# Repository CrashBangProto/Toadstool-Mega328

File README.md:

#Toadstool-Mega328

**Toadstool Development Board - ATmega328P**

The Toadstool family is made up of breadboard-friendly prototyping boards that house a microcontroller, and modules called *Caps* that connect using a standard header.  The prototyping board is analagous to an Arduino/Launchpad and the Cap analagous to a shield/boosterpack.

This repository contains the schematics for the **Toadstool-Mega328** prototyping board, a breadboard-friendly PCB that houses the ATmega328P microcontroller (or other Atmel pin-compatible variants such as the ATmega8/48/88/168/328).

The boards were layed out using [KiCad](http://www.kicad-pcb.org) - KiCad is open source and awesome.

There are a number of other CrashBangProto respositories containing the schematics for other Toadstool boards and Caps, as well as sample code to get you up and running.

Visit the [Toadstool Webpages](http://www.crash-bang.com/projects/toadstool/) for more information on the project.

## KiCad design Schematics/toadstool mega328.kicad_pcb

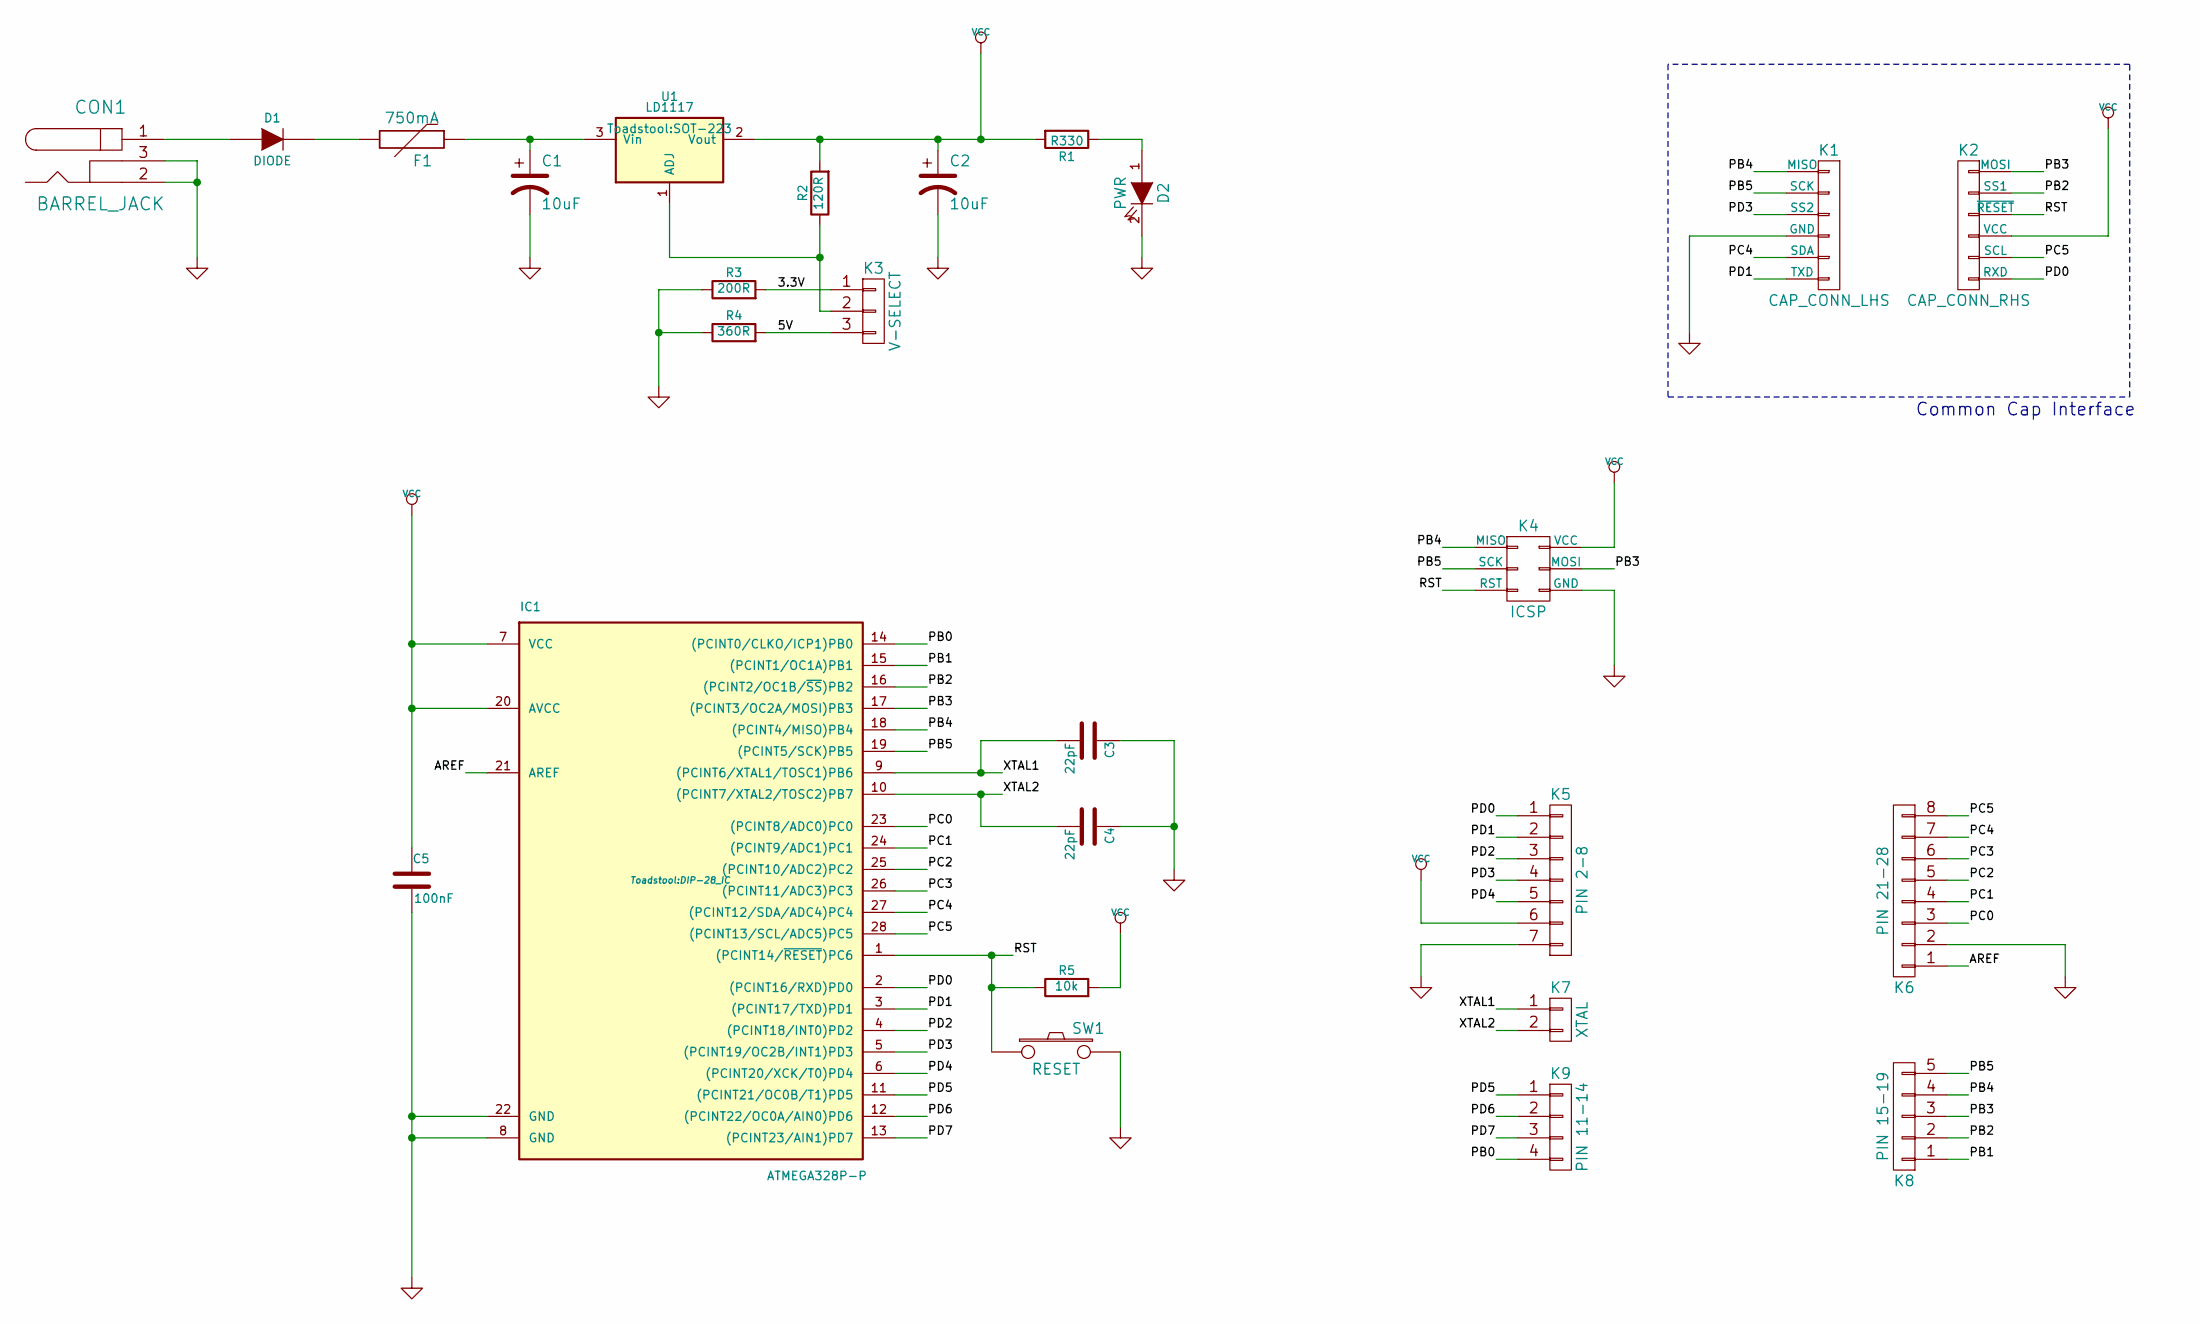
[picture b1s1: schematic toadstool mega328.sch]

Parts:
C1, C2: 10uF; c_elec_4x5.3
C3, C4: 22pF; C_0805_HandSoldering
C5: 100nF; C_0805_HandSoldering
CON1: BARREL_JACK; BARREL_JACK_No_Slot
D1: DIODE; Diode_D3
D2: PWR; LED-0805
F1: 750mA; MiniSMDPTC-4532
IC1: ATMEGA328P-P; DIP-28_IC
K1: CAP_CONN_LHS; Socket_Strip_Straight_1x06
K2: CAP_CONN_RHS; Socket_Strip_Straight_1x06
K3: V-SELECT; Pin_Header_Straight_1x03
K4: ICSP; ICSP_Header_2x03
K5: PIN 2-8; Pin_Header_Straight_1x07
K6: PIN 21-28; Pin_Header_Straight_1x08
K7: XTAL; Socket_Strip_Straight_1x02
K8: PIN 15-19; Pin_Header_Straight_1x05
K9: PIN 11-14; Pin_Header_Straight_1x04
R1: R330; R_0805_HandSoldering
R2: 120R; R_0805_HandSoldering
R3: 200R; R_0805_HandSoldering
R4: 360R; R_0805_HandSoldering
R5: 10k; R_0805_HandSoldering
SW1: RESET; Switch_SMT_Alps_SKQGAxE010
U1: LD1117; SOT-223

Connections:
/3.3V: K3.1, R3.2
/5V: K3.3, R4.2
/AREF: IC1.21 (AREF), K6.1
/PB0: IC1.14 ((PCINT0/CLKO/ICP1)PB0), K9.4
/PB1: IC1.15 ((PCINT1/OC1A)PB1), K8.1
/PB2: IC1.16 ((PCINT2/OC1B/~SS~)PB2), K2.2 (SS1), K8.2
/PB3: IC1.17 ((PCINT3/OC2A/MOSI)PB3), K2.1 (MOSI), K4.4 (MOSI), K8.3
/PB4: IC1.18 ((PCINT4/MISO)PB4), K1.1 (MISO), K4.1 (MISO), K8.4
/PB5: IC1.19 ((PCINT5/SCK)PB5), K1.2 (SCK), K4.3 (SCK), K8.5
/PC0: IC1.23 ((PCINT8/ADC0)PC0), K6.3
/PC1: IC1.24 ((PCINT9/ADC1)PC1), K6.4
/PC2: IC1.25 ((PCINT10/ADC2)PC2), K6.5
/PC3: IC1.26 ((PCINT11/ADC3)PC3), K6.6
/PC4: IC1.27 ((PCINT12/SDA/ADC4)PC4), K1.5 (SDA), K6.7
/PC5: IC1.28 ((PCINT13/SCL/ADC5)PC5), K2.5 (SCL), K6.8
/PD0: IC1.2 ((PCINT16/RXD)PD0), K2.6 (RXD), K5.1
/PD1: IC1.3 ((PCINT17/TXD)PD1), K1.6 (TXD), K5.2
/PD2: IC1.4 ((PCINT18/INT0)PD2), K5.3
/PD3: IC1.5 ((PCINT19/OC2B/INT1)PD3), K1.3 (SS2), K5.4
/PD4: IC1.6 ((PCINT20/XCK/T0)PD4), K5.5
/PD5: IC1.11 ((PCINT21/OC0B/T1)PD5), K9.1
/PD6: IC1.12 ((PCINT22/OC0A/AIN0)PD6), K9.2
/PD7: IC1.13 ((PCINT23/AIN1)PD7), K9.3
/RST: IC1.1 ((PCINT14/~RESET~)PC6), K2.3 (~RESET), K4.5 (RST), R5.1, SW1.1
/XTAL1: C3.2, IC1.9 ((PCINT6/XTAL1/TOSC1)PB6), K7.1
/XTAL2: C4.2, IC1.10 ((PCINT7/XTAL2/TOSC2)PB7), K7.2
GND: C1.2, C2.2, C3.1, C4.1, C5.2, CON1.2, CON1.3, D2.2 (K), IC1.8 (GND), IC1.22 (GND), K1.4 (GND), K4.6 (GND), K5.7, K6.2, R3.1, R4.1, SW1.2
unnamed: C1.1, F1.1, U1.3 (Vin)
unnamed: CON1.1, D1.1 (A)
unnamed: D1.2 (K), F1.2
unnamed: D2.1 (A), R1.1
unnamed: K3.2, R2.1, U1.1 (ADJ)
VCC: C2.1, C5.1, IC1.7 (VCC), IC1.20 (AVCC), K2.4 (VCC), K4.2 (VCC), K5.6, R1.2, R2.2, R5.2, U1.2 (Vout)

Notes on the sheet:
Common Cap Interface

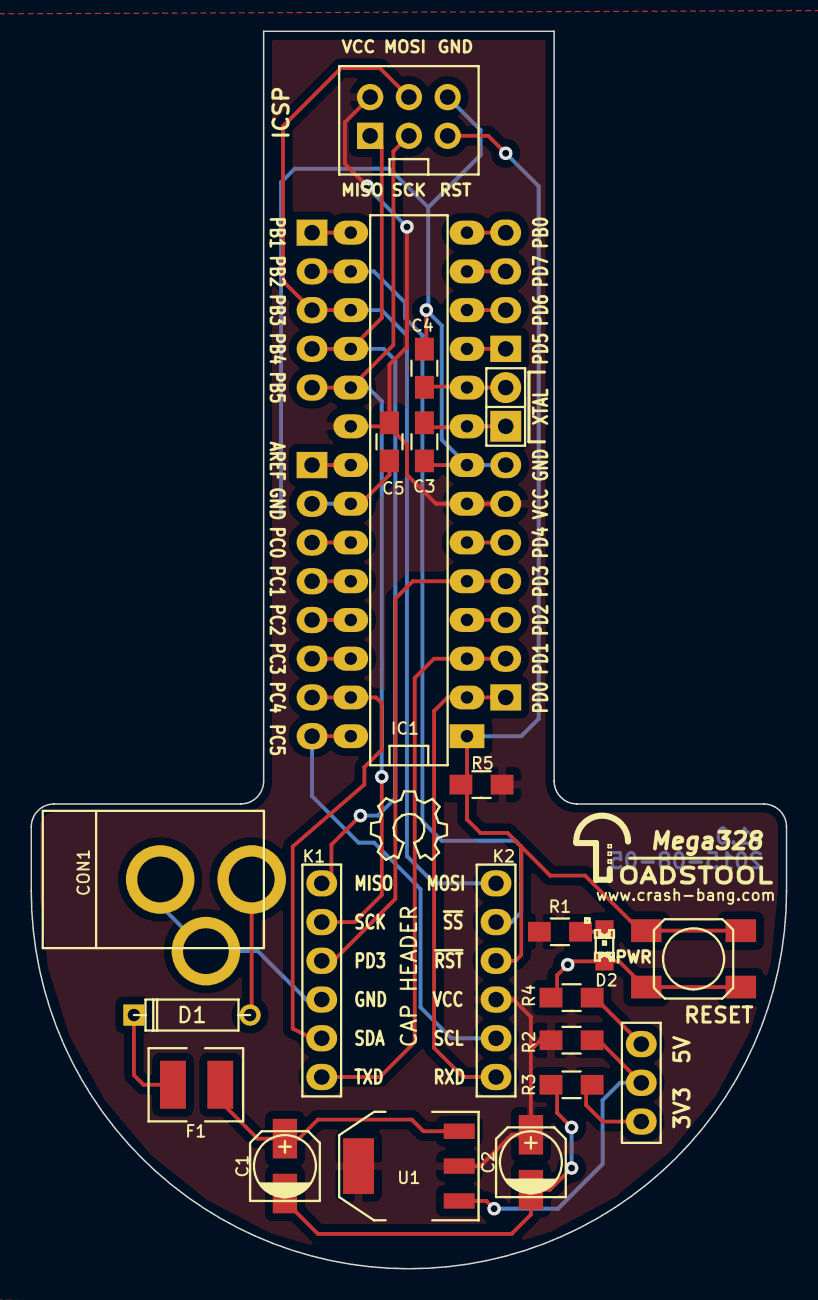
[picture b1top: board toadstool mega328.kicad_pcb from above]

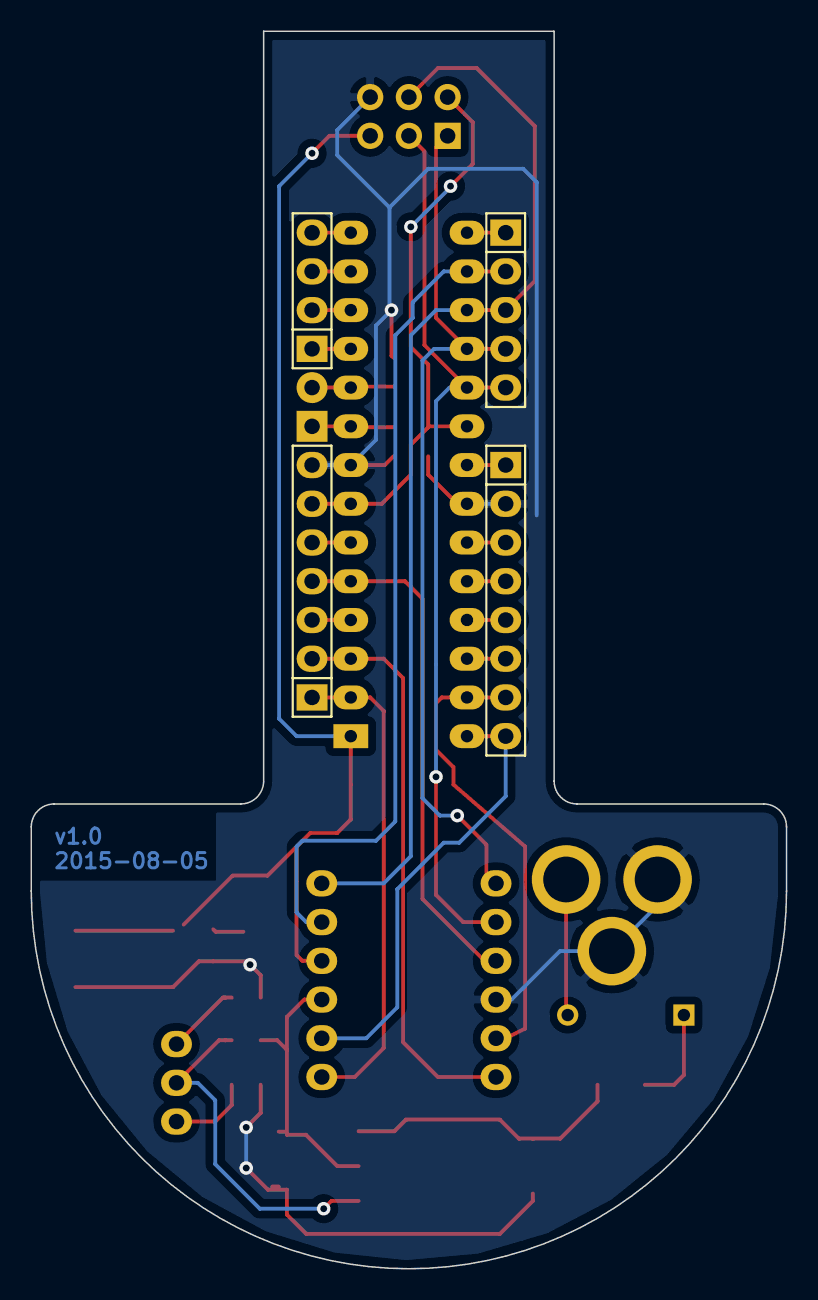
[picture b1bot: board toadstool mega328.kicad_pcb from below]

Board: 2 copper layers, 49.5 x 81.2 mm, 27 parts (4 on the bottom side), 33 nets.

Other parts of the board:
Toadstool_Logo: LOGO**; Toadstool_Logo

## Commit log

2015-01-01 :lollipop: Added .gitattributes & .gitignore files
2015-01-01 Initial Commit - v0.1
    Version 0.1
    Original PCB layouts sent to PCB fab for prototyping round 1
2015-01-01 Correct gitignore
    Corrected to exclude certain files
2015-01-01 Removed files not to be tracked
2015-02-17 Cosmetic
    Rounding of board corners
    Change logo
2015-03-04 Components Changed
    Updated Power Jack and Reset button with 3D models.
    Minor changes to silkscreen
2015-03-24 Version 0.2 - Updates from v0.1 prototype
    Final changes from v0.1 prototype:
    - Add aluminium caps
    - Silkscreen cosmetics
2015-03-24 Delete toadstool mega328.kicad_pcb-bak
    Delete backup
2015-03-31 Cap Header
    Widening of Cap Header
2015-05-15 Final Prototype Commit
2015-05-15 Update Readme and gitignore
2015-08-19 Cosmetic Changes to Silkscreen
    Cosmetic Changes to Silkscreen
